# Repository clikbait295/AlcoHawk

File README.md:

# AlcoHawk
All design files for my science research project titled "Measuring Blood Alcohol Concentration With Near-Infrared Spectroscopy."

<br />This work is licensed under a <a rel="license" href="http://creativecommons.org/licenses/by-nc-sa/4.0/">Creative Commons Attribution-NonCommercial-ShareAlike 4.0 International License</a>.

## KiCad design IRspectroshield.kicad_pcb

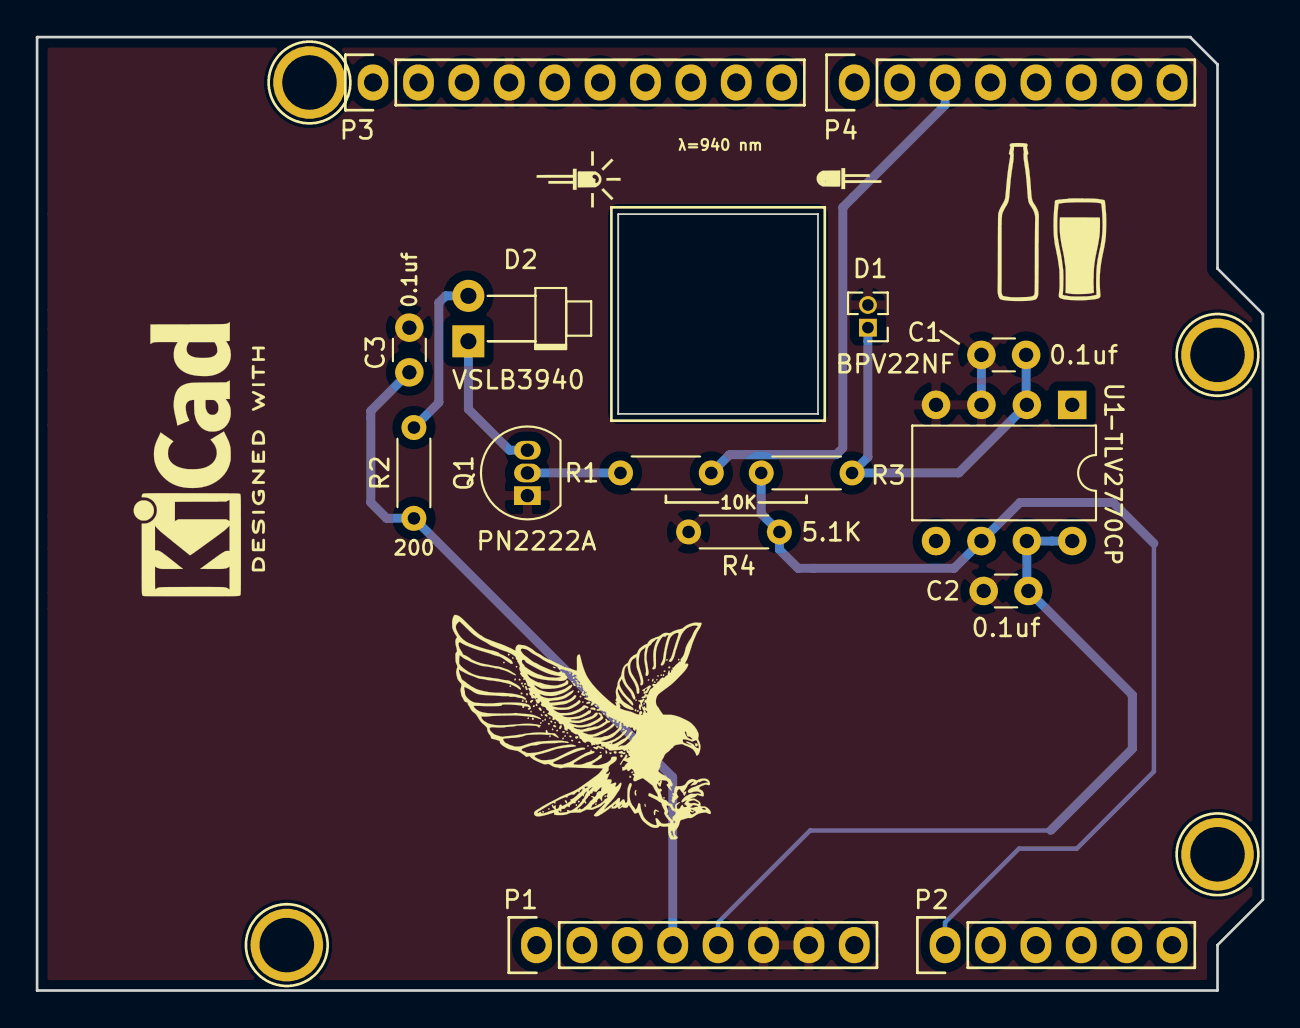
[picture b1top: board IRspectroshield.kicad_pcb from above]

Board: 2 copper layers, 68.6 x 53.3 mm, 19 parts (0 on the bottom side), 9 nets.

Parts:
C1, C2, C3: 0.1uf; C_Disc_D3.0mm_W1.6mm_P2.50mm
D1: BPV22NF; PinHeader_1x02_P1.27mm_Vertical
D2: VSLB3940; LED_D1.8mm_W1.8mm_H2.4mm_Horizontal_O3.81mm_Z1.6mm
P1: Power; Socket_Strip_Arduino_1x08
P2: Analog; Socket_Strip_Arduino_1x06
P3: Digital; Socket_Strip_Arduino_1x10
P4: Digital; Socket_Strip_Arduino_1x08
P5, P6, P7, P8: CONN_01X01; Arduino_1pin
Q1: PN2222A; TO-92_Inline
R1, R3: 10K; R_Axial_DIN0204_L3.6mm_D1.6mm_P5.08mm_Horizontal
R2: 200; R_Axial_DIN0204_L3.6mm_D1.6mm_P5.08mm_Horizontal
R4: 5.1K; R_Axial_DIN0204_L3.6mm_D1.6mm_P5.08mm_Horizontal
U1: -TLV2770CP; DIP-8_W7.62mm

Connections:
+3V3: C3.2, P1.4, R2.1
+5V: C2.2, P1.5, U1.7, U1.8
/5(**): P4.3, R1.2
/A0: P2.1, R3.2, R4.2, U1.6
GND: C1.1, C2.1, C3.1, D1.2, P1.6, P1.7, P3.4, Q1.1, R4.1, U1.3, U1.4
unnamed: C1.2, D1.1, R3.1, U1.2
unnamed: D2.1, Q1.3
unnamed: D2.2, R2.2
unnamed: Q1.2, R1.1

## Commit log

2022-02-06 Create LICENSE
2022-02-06 Fixed comment
